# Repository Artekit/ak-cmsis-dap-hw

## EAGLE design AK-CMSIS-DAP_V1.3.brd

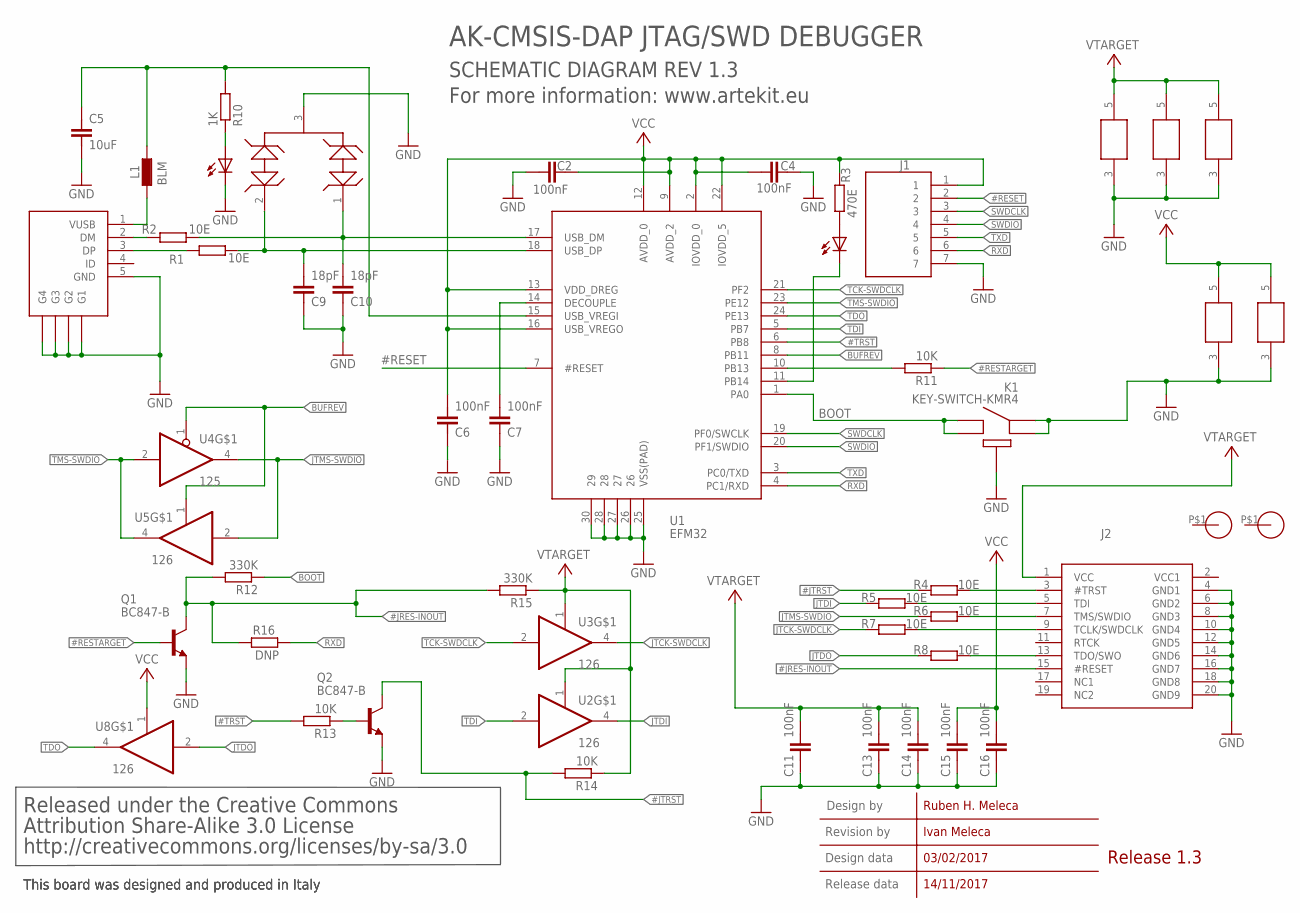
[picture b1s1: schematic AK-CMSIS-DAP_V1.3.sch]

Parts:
C2, C4, C6, C7, C11, C13, C14, C15, C16: 100nF; C0603
C5: 10uF; C0805
C9, C10: 18pF; C0603
D1: D5V0L; SOT-23-3
J1: CON-PH-1X07-P0.1"1; PIN-HEADER-1X07
J2: CONN-JTAG-20PIN-SMD; PIN-HEADER-2X10-WURTH
K1: KEY-SWITCH-KMR4; KEY-SWITCH-KMR-SERIES
L1: BLM; I0603
Q1, Q2: BC847-B; SOT-23-3
R1, R2, R4, R5, R6, R7, R8: 10E; R0603
R3: 470E; R0603
R10: 1K; R0603
R11, R13, R14: 10K; R0603
R12, R15: 330K; R0603
R16: DNP; R0603
U1: EFM32; QFN24-5X5-P0.65; MPN EFM32HG308F64G-B-QFN24
U2, U3, U5, U8: 126; SOT363-5
U4: 125; SOT363-5
U$1: CON-USB-MINI-B-SMD; MPN 690-005-299-043
U$2, U$4: LED0603-RED; CHIPLED_0603
U$3, U$5: FIDUTIAL_1.2MM

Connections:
#JRES-INOUT: J2.15 (#RESET), Q1.3, R12.2, R15.2, R16.2
#JTRST: Q2.3, R4.2, R14.2
#RESET: J1.2, U1.7 (#RESET)
#RESTARGET: Q1.1, R11.1
#TRST: R13.2, U1.6 (PB8)
BOOT: K1.3, K1.4, R12.1, U1.1 (PA0)
BUFREV: U1.8 (PB11), U4.1 (EN), U5.1 (EN)
GND: C2.1, C4.2, C5.2, C6.1, C7.1, C9.1, C10.1, C11.1, C13.1, C14.1, C15.1, C16.1, D1.3, J1.7, J2.4 (GND1), J2.6 (GND2), J2.8 (GND3), J2.10 (GND4), J2.12 (GND5), J2.14 (GND6), J2.16 (GND7), J2.18 (GND8), J2.20 (GND9), K1.1, K1.2, K1.5, Q1.2, Q2.2, U1.25 (VSS(PAD)), U1.26, U1.27, U1.28, U1.30 (29), U2.3 (GND), U3.3 (GND), U4.3 (GND), U5.3 (GND), U8.3 (GND), U$1.5 (GND), U$1.C (G1), U$1.D (G2), U$1.E (G3), U$1.F (G4), U$2.C
JTCK-SWDCLK: R7.2, U3.4 (O)
JTDI: R5.2, U2.4 (O)
JTDO: R8.2, U8.2 (I)
JTMS-SWDIO: R6.2, U4.4 (O), U5.2 (I)
unnamed: R2.1, U$1.2 (DM)
unnamed: R1.1, U$1.3 (DP)
unnamed: C10.2, D1.1, R2.2, U1.17 (USB_DM)
unnamed: C9.2, D1.2, R1.2, U1.18 (USB_DP)
unnamed: L1.1, U$1.1 (VUSB)
unnamed: C5.1, L1.2, R10.2, U1.15 (USB_VREGI)
unnamed: C7.2, U1.14 (DECOUPLE)
unnamed: J2.3 (#TRST), R4.1
unnamed: R3.1, U$4.A
unnamed: J2.5 (TDI), R5.1
unnamed: U1.11 (PB14), U$4.C
unnamed: J2.7 (TMS/SWDIO), R6.1
unnamed: J2.9 (TCLK/SWDCLK), R7.1
unnamed: J2.13 (TDO/SWO), R8.1
unnamed: R10.1, U$2.A
unnamed: R11.2, U1.10 (PB13)
unnamed: Q2.1, R13.1
RXD: J1.6, R16.1, U1.4 (PC1/RXD)
SWDCLK: J1.3, U1.19 (PF0/SWCLK)
SWDIO: J1.4, U1.20 (PF1/SWDIO)
TCK-SWDCLK: U1.21 (PF2), U3.2 (I)
TDI: U1.5 (PB7), U2.2 (I)
TDO: U1.24 (PE13), U8.4 (O)
TMS-SWDIO: U1.23 (PE12), U4.2 (I), U5.4 (O)
TXD: J1.5, U1.3 (PC0/TXD)
VCC: C2.2, C4.1, C6.2, C15.2, C16.2, J1.1, R3.2, U1.2 (IOVDD_0), U1.9 (AVDD_2), U1.12 (AVDD_0), U1.13 (VDD_DREG), U1.16 (USB_VREGO), U1.22 (IOVDD_5), U5.5 (VCC), U8.1 (EN), U8.5 (VCC)
VTARGET: C11.2, C13.2, C14.2, J2.1 (VCC), R14.1, R15.1, U2.1 (EN), U2.5 (VCC), U3.1 (EN), U3.5 (VCC), U4.5 (VCC)

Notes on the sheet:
AK-CMSIS-DAP JTAG/SWD DEBUGGER
SCHEMATIC DIAGRAM REV 1.3
For more information: www.artekit.eu
This board was designed and produced in Italy
Released under the Creative Commons
Attribution Share-Alike 3.0 License
http://creativecommons.org/licenses/by-sa/3.0
03/02/2017
14/11/2017
Ivan Meleca
Ruben H. Meleca
Design by
Revision by
Design data
Release data
Release 1.3

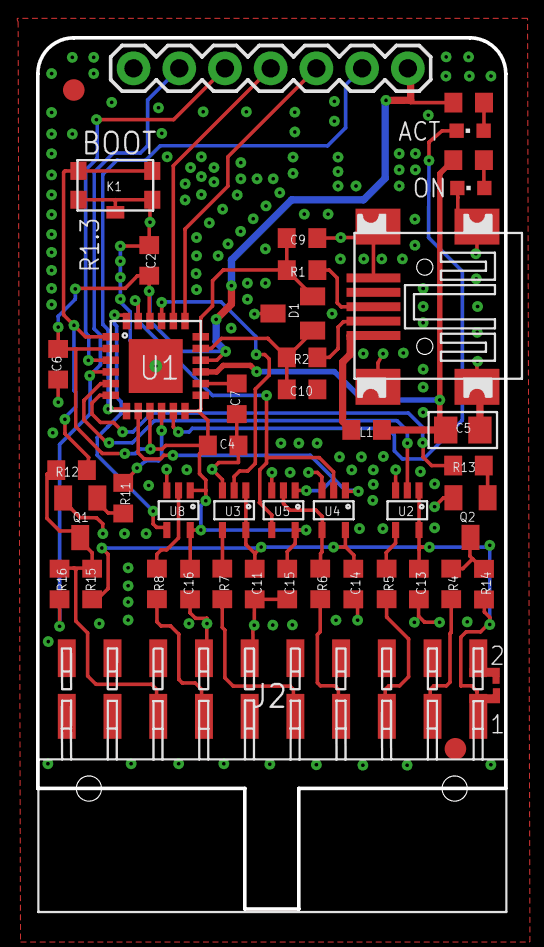
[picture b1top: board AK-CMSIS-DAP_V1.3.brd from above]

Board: 2 copper layers, 26.0 x 48.4 mm, 45 parts (0 on the bottom side), 39 nets.

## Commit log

2018-01-13 :lollipop: Added .gitattributes & .gitignore files
